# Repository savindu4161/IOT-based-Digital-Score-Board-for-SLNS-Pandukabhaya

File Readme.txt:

******//REMOTELY OPERATED LOW COST DIGITAL SCORE BOARD\\****** 
            *****//MADE BY NEW DESIGN CENTER(E)\\*****

This design consist with ESP8266 based single Master circuit and Arduino Nano based multiple Slave circuits.
Each slave microcontroller is having unique device address.

Team A  : @
Team B  : ^
Score A : $
Score B : &
Set A   : %
Set B   : z
Time    : T

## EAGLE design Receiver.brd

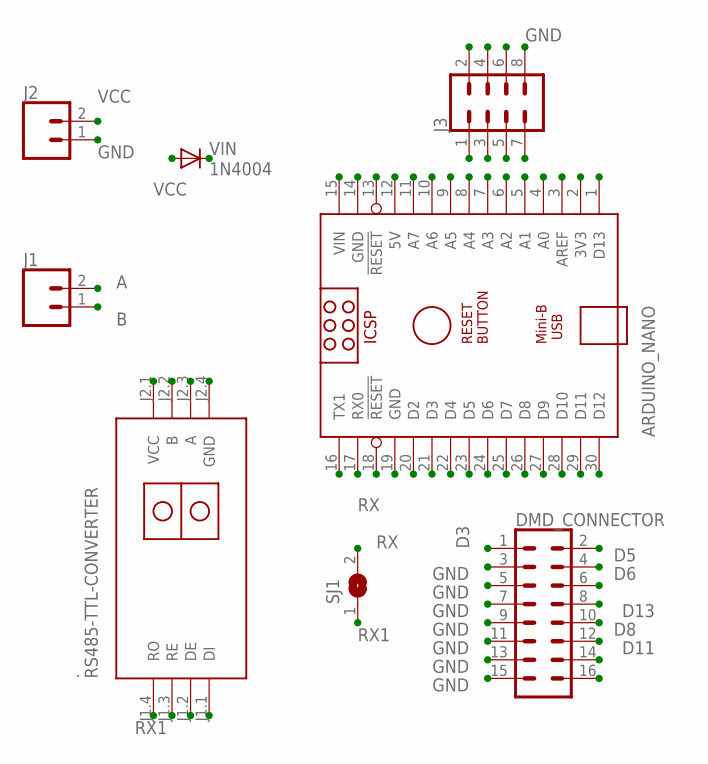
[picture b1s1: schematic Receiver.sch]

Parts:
.: RS485-TTL-CONVERTER
ARDUINO_NANO: ARDUINO_NANO
DMD_CONNECTOR: CONN_08X2_HEADER; 2X8
J1, J2: CONN_025MM; SCREWTERMINAL-5MM-2
J3: CONN_04X2; 2X4
SJ1: SJW
VIN: 1N4004; DO41-10

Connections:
A: ..J2.3 (A), J1.2
A1: ARDUINO_NANO.5 (A1), J3.7
A2: ARDUINO_NANO.6 (A2), J3.5
A3: ARDUINO_NANO.7 (A3), J3.3
A4: ARDUINO_NANO.8 (A4), J3.1
B: ..J2.2 (B), J1.1
D3: ARDUINO_NANO.21 (D3), DMD_CONNECTOR.1
D5: ARDUINO_NANO.23 (D5), DMD_CONNECTOR.2
D6: ARDUINO_NANO.24 (D6), DMD_CONNECTOR.4
D7: ARDUINO_NANO.25 (D7)
D8: ARDUINO_NANO.26 (D8), DMD_CONNECTOR.10
D9: ARDUINO_NANO.27 (D9)
D11: ARDUINO_NANO.29 (D11), DMD_CONNECTOR.12
D13: ARDUINO_NANO.1 (D13), DMD_CONNECTOR.8
GND: ..J1.2 (DE), ..J1.3 (RE), ..J2.4 (GND), ARDUINO_NANO.14 (GND), DMD_CONNECTOR.3, DMD_CONNECTOR.5, DMD_CONNECTOR.7, DMD_CONNECTOR.9, DMD_CONNECTOR.11, DMD_CONNECTOR.13, DMD_CONNECTOR.15, J2.1, J3.2, J3.4, J3.6, J3.8
RX: ARDUINO_NANO.17 (RX0), SJ1.2
RX1: ..J1.4 (RO), SJ1.1
VCC: J2.2, VIN.A
VIN: ..J2.1 (VCC), ARDUINO_NANO.15 (VIN), VIN.C

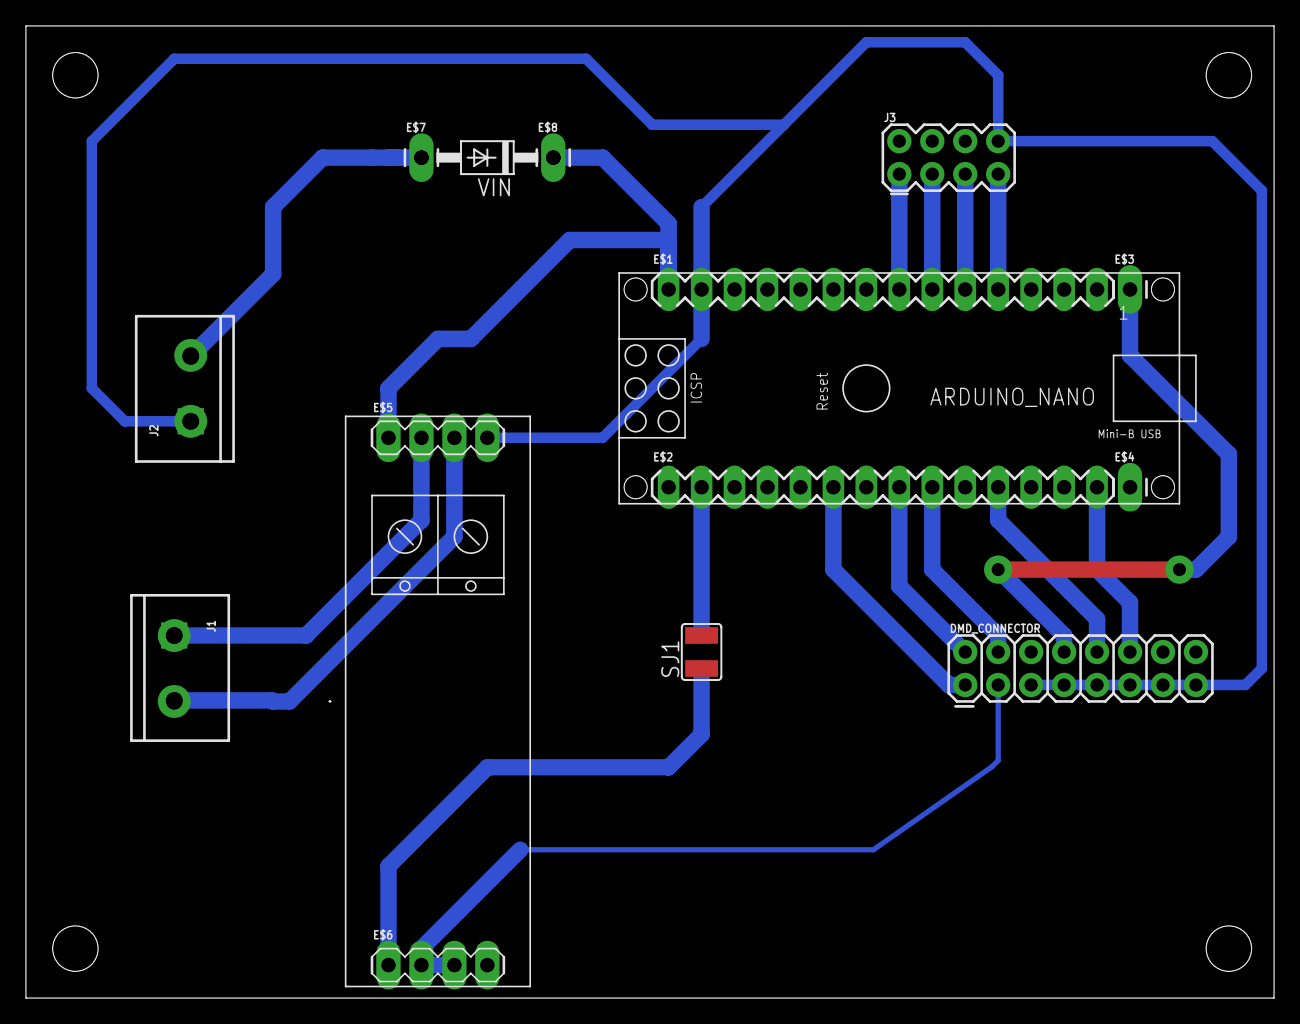
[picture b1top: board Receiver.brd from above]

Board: 2 copper layers, 96.2 x 74.9 mm, 16 parts (0 on the bottom side), 17 nets.

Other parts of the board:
E$1, E$2: 1X14-LONGPADS
E$3, E$4, E$7, E$8: 1X01_LONGPAD
E$5, E$6: 1X04_LONGPADS

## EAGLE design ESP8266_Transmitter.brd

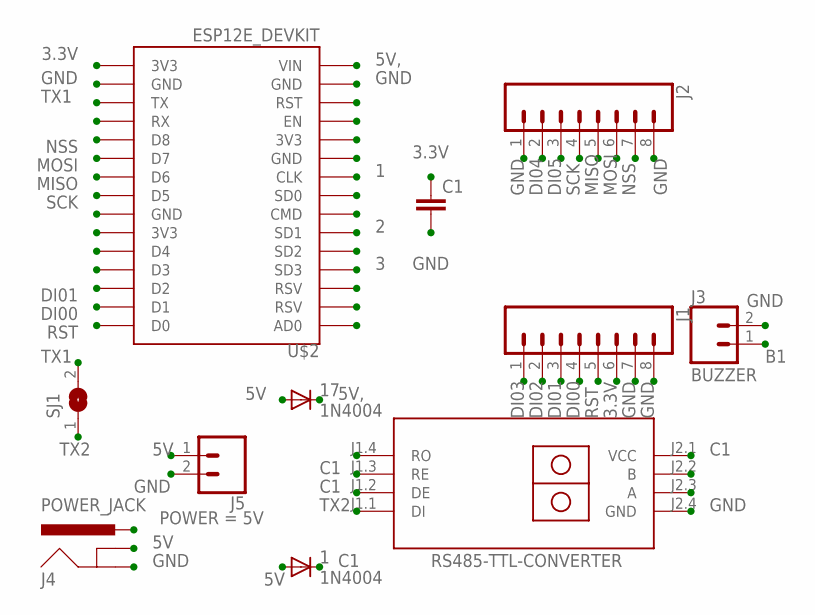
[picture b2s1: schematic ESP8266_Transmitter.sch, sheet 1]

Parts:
1, 17: 1N4004; DO41-10
C1: C5/3; C5B3
J1, J2: CONN_08LONGPADS; 1X08_LONGPADS
J3, J5: CONN_025MM; SCREWTERMINAL-5MM-2
J4: POWER_JACK; POWER_JACK_PTH
RS485-TTL-CONVERTER: RS485-TTL-CONVERTER
SJ1: SJ
U$2: ESP12E_DEVKIT

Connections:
1: U$2.CLK
2: U$2.SD1
3: U$2.SD3
3.3V: C1.1, J1.6, U$2.3V3@2 (3V3)
5V: 1.A, 17.A, J4.PWR, J5.1
5V,: 17.C, U$2.VIN
B1: J3.1
C1: 1.C, RS485-TTL-CONVERTER.J1.2 (DE), RS485-TTL-CONVERTER.J1.3 (RE), RS485-TTL-CONVERTER.J2.1 (VCC)
DI00: J1.4, U$2.D1
DI01: J1.3, U$2.D2
DI02: J1.2
DI03: J1.1
DI04: J2.2
DI05: J2.3
GND: C1.2, J1.7, J1.8, J2.1, J2.8, J3.2, J4.GNDBREAK, J5.2, RS485-TTL-CONVERTER.J2.4 (GND), U$2.GND@1 (GND), U$2.GND@3 (GND)
MISO: J2.5, U$2.D6
MOSI: J2.6, U$2.D7
NSS: J2.7, U$2.D8
RS485-TTL-CONVERTER: RS485-TTL-CONVERTER.J1.4 (RO)
RST: J1.5, U$2.D0
SCK: J2.4, U$2.D5
TX1: SJ1.2, U$2.TX
TX2: RS485-TTL-CONVERTER.J1.1 (DI), SJ1.1

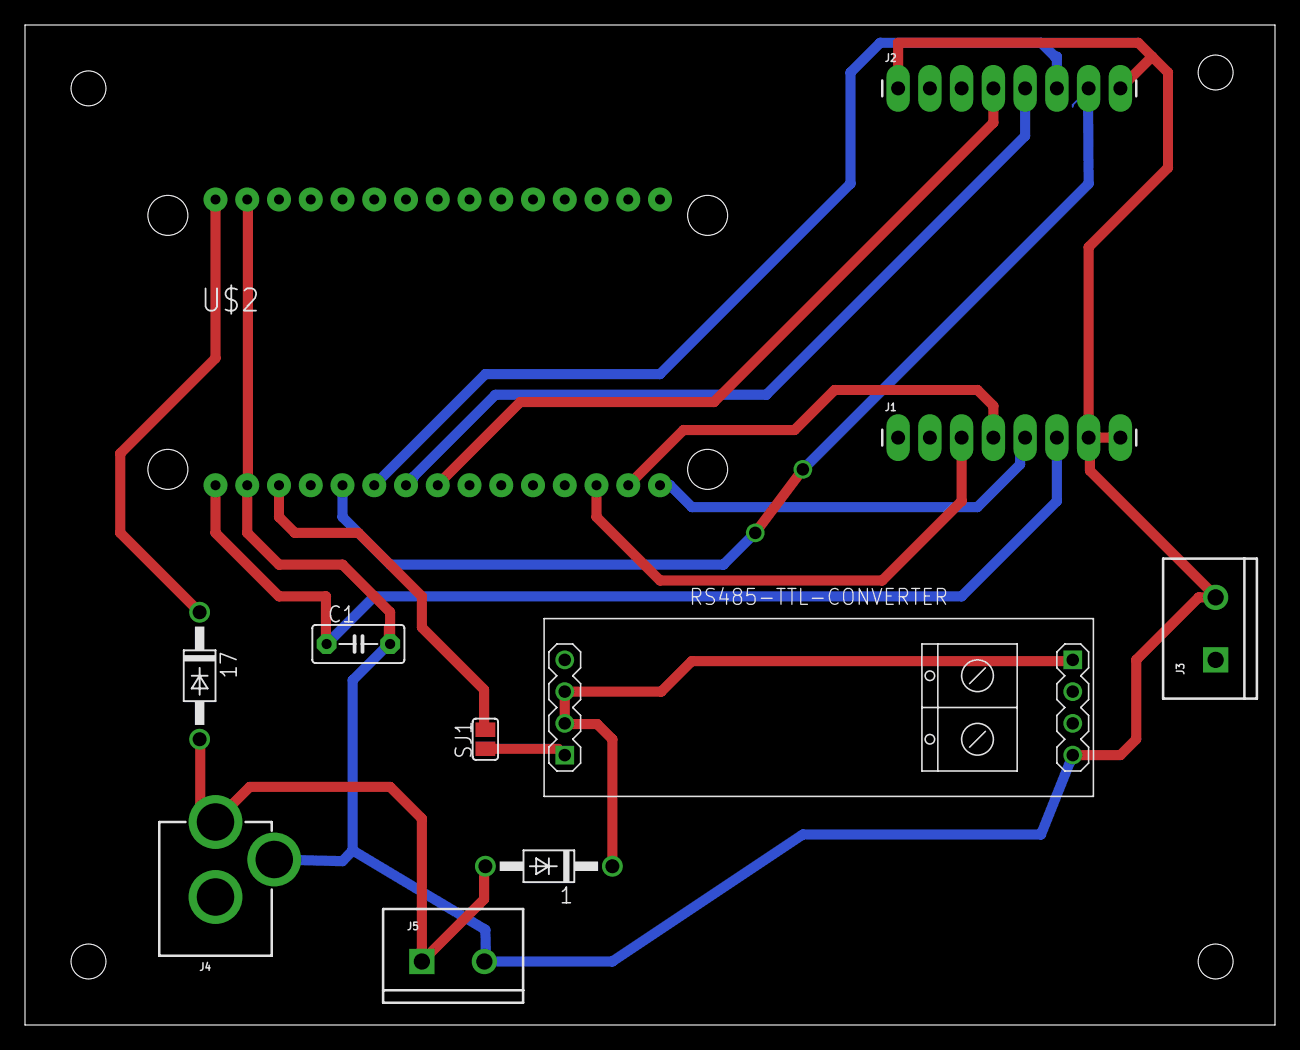
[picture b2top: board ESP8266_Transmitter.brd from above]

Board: 2 copper layers, 100.0 x 80.0 mm, 11 parts (0 on the bottom side), 14 nets.

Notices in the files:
parts and their libraries:
SparkFun-Connectors: Licensing: Creative Commons ShareAlike 4.0 International - https://creativecommons.org/licenses/by-sa/4.0
diy-modules: Released under the Creative Commons Attribution 4.0 International License: http://creativecommons.org/licenses/by/4.0
